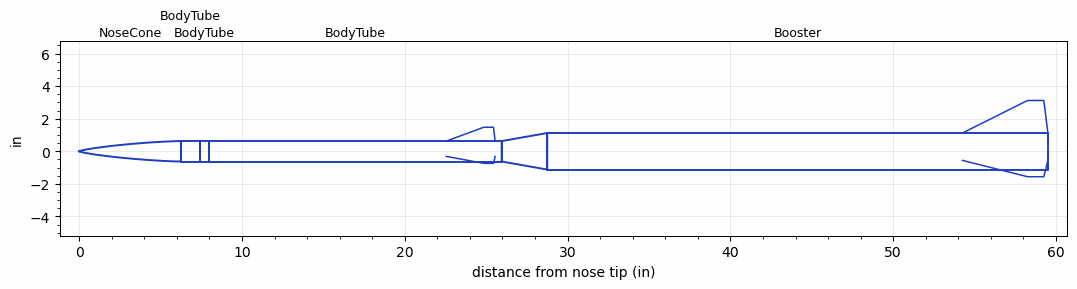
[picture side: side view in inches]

<RASAeroDocument>
 <FileVersion>2</FileVersion>
 <RocketDesign>
  <NoseCone>
   <Length>6.25</Length>
   <Diameter>1.255</Diameter>
   <Shape>Von Karman Ogive</Shape>
   <Location>0</Location>
  </NoseCone>
  <BodyTube>
   <Length>1.2</Length>
   <Diameter>1.255</Diameter>
   <Location>6.25</Location>
  </BodyTube>
  <BodyTube>
   <Length>0.5</Length>
   <Diameter>1.255</Diameter>
   <Location>7.45</Location>
  </BodyTube>
  <BodyTube>
   <Length>18</Length>
   <Diameter>1.255</Diameter>
   <Location>7.95</Location>
   <Fin>
    <Count>3</Count>
    <Chord>3</Chord>
    <Span>0.85</Span>
    <SweepDistance>2.3</SweepDistance>
    <TipChord>0.6</TipChord>
    <Thickness>0.096</Thickness>
    <LERadius>0.015</LERadius>
    <Location>3.4</Location>
    <AirfoilSection>Hexagonal</AirfoilSection>
    <FX1>0.15</FX1>
    <FX3>0.15</FX3>
   </Fin>
  </BodyTube>
  <Booster>
   <Length>30.75</Length>
   <Diameter>2.242</Diameter>
   <InsideDiameter>1.255</InsideDiameter>
   <RailGuideDiameter>0.438</RailGuideDiameter>
   <RailGuideHeight>0.298</RailGuideHeight>
   <Location>25.95</Location>
   <ShoulderLength>2.8</ShoulderLength>
   <Fin>
    <Count>3</Count>
    <Chord>5.25</Chord>
    <Span>2</Span>
    <SweepDistance>4</SweepDistance>
    <TipChord>1</TipChord>
    <Thickness>0.096</Thickness>
    <LERadius>0.015</LERadius>
    <Location>5.25</Location>
    <AirfoilSection>Hexagonal</AirfoilSection>
    <FX1>0.2</FX1>
    <FX3>0.2</FX3>
   </Fin>
  </Booster>
  <Surface>Camouflage Paint</Surface>
  <ModifiedBarrowman>True</ModifiedBarrowman>
  <Turbulence>True</Turbulence>
  <UseBooster1>True</UseBooster1>
  <UseBooster2>False</UseBooster2>
 </RocketDesign>
 <LaunchSite>
  <Altitude>850</Altitude>
  <Pressure>29.02</Pressure>
  <RodAngle>2</RodAngle>
  <RodLength>6</RodLength>
  <Temperature>55.97</Temperature>
  <WindSpeed>8</WindSpeed>
 </LaunchSite>
 <Recovery>
  <Altitude1>656.168</Altitude1>
  <Altitude2>700</Altitude2>
  <DeviceType1>Parachute</DeviceType1>
  <DeviceType2>Parachute</DeviceType2>
  <Event1>True</Event1>
  <Event2>True</Event2>
  <Size1>9</Size1>
  <Size2>24</Size2>
  <EventType1>Apogee</EventType1>
  <EventType2>Altitude</EventType2>
  <CD1>0.5</CD1>
  <CD2>0</CD2>
 </Recovery>
 <SimulationList>
  <Simulation>
   <SustainerEngine>Dart  (NoThrust)</SustainerEngine>
   <SustainerLaunchWt>1.32</SustainerLaunchWt>
   <SustainerCG>14.08</SustainerCG>
   <SustainerIgnitionDelay>0</SustainerIgnitionDelay>
   <Booster1Engine>J540R  (AT)</Booster1Engine>
   <Booster1LaunchWt>5.96</Booster1LaunchWt>
   <Booster1SeparationDelay>0</Booster1SeparationDelay>
   <Booster1IgnitionDelay>0</Booster1IgnitionDelay>
   <Booster1CG>38</Booster1CG>
   <IncludeBooster1>True</IncludeBooster1>
   <Booster2Delay>0</Booster2Delay>
   <IncludeBooster2>False</IncludeBooster2>
   <TimetoApogee>21.33034</TimetoApogee>
   <MaxAltitude>9448.087</MaxAltitude>
   <MaxVelocity>1171.424</MaxVelocity>
  </Simulation>
  <Simulation>
   <SustainerEngine>Dart  (NoThrust)</SustainerEngine>
   <SustainerLaunchWt>1.23</SustainerLaunchWt>
   <SustainerCG>13.2</SustainerCG>
   <SustainerIgnitionDelay>0</SustainerIgnitionDelay>
   <Booster1Engine>J449BS  (CTI)</Booster1Engine>
   <Booster1LaunchWt>5.95</Booster1LaunchWt>
   <Booster1SeparationDelay>0</Booster1SeparationDelay>
   <Booster1IgnitionDelay>0</Booster1IgnitionDelay>
   <Booster1CG>38.4</Booster1CG>
   <IncludeBooster1>True</IncludeBooster1>
   <Booster2Delay>0</Booster2Delay>
   <IncludeBooster2>False</IncludeBooster2>
   <TimetoApogee>23.11037</TimetoApogee>
   <MaxAltitude>10923.64</MaxAltitude>
   <MaxVelocity>1266.204</MaxVelocity>
  </Simulation>
  <Simulation>
   <SustainerEngine>Dart  (NoThrust)</SustainerEngine>
   <SustainerLaunchWt>1.28</SustainerLaunchWt>
   <SustainerCG>11.27</SustainerCG>
   <SustainerIgnitionDelay>0</SustainerIgnitionDelay>
   <Booster1Engine>J760-WT-19A  (CTI)</Booster1Engine>
   <Booster1LaunchWt>5.9</Booster1LaunchWt>
   <Booster1SeparationDelay>0</Booster1SeparationDelay>
   <Booster1IgnitionDelay>0</Booster1IgnitionDelay>
   <Booster1CG>38.8</Booster1CG>
   <IncludeBooster1>True</IncludeBooster1>
   <Booster2Delay>0</Booster2Delay>
   <IncludeBooster2>False</IncludeBooster2>
   <TimetoApogee>22.99039</TimetoApogee>
   <MaxAltitude>11204.15</MaxAltitude>
   <MaxVelocity>1428.314</MaxVelocity>
  </Simulation>
  <Simulation>
   <SustainerEngine>G75J  (AT)</SustainerEngine>
   <SustainerLaunchWt>1.8</SustainerLaunchWt>
   <SustainerCG>14.12</SustainerCG>
   <SustainerIgnitionDelay>0</SustainerIgnitionDelay>
   <Booster1Engine>J760-WT-19A  (CTI)</Booster1Engine>
   <Booster1LaunchWt>6.4</Booster1LaunchWt>
   <Booster1SeparationDelay>0</Booster1SeparationDelay>
   <Booster1IgnitionDelay>0</Booster1IgnitionDelay>
   <Booster1CG>37.38</Booster1CG>
   <IncludeBooster1>True</IncludeBooster1>
   <Booster2Delay>0</Booster2Delay>
   <IncludeBooster2>False</IncludeBooster2>
   <TimetoApogee>28.0205</TimetoApogee>
   <MaxAltitude>16573.13</MaxAltitude>
   <MaxVelocity>1517.604</MaxVelocity>
  </Simulation>
  <Simulation>
   <SustainerEngine>Dart  (NoThrust)</SustainerEngine>
   <SustainerLaunchWt>1.27</SustainerLaunchWt>
   <SustainerCG>11.18</SustainerCG>
   <SustainerIgnitionDelay>0</SustainerIgnitionDelay>
   <Booster1Engine>K530SS  (CTI)</Booster1Engine>
   <Booster1LaunchWt>7.12</Booster1LaunchWt>
   <Booster1SeparationDelay>0</Booster1SeparationDelay>
   <Booster1IgnitionDelay>0</Booster1IgnitionDelay>
   <Booster1CG>40.54</Booster1CG>
   <IncludeBooster1>True</IncludeBooster1>
   <Booster2Delay>0</Booster2Delay>
   <IncludeBooster2>False</IncludeBooster2>
   <TimetoApogee>23.54038</TimetoApogee>
   <MaxAltitude>11219.02</MaxAltitude>
   <MaxVelocity>1350.228</MaxVelocity>
  </Simulation>
  <Simulation>
   <SustainerEngine>Dart  (NoThrust)</SustainerEngine>
   <SustainerLaunchWt>1.27</SustainerLaunchWt>
   <SustainerCG>11.19</SustainerCG>
   <SustainerIgnitionDelay>0</SustainerIgnitionDelay>
   <Booster1Engine>J800T  (AT)</Booster1Engine>
   <Booster1LaunchWt>5.9</Booster1LaunchWt>
   <Booster1SeparationDelay>0</Booster1SeparationDelay>
   <Booster1IgnitionDelay>0</Booster1IgnitionDelay>
   <Booster1CG>38.95</Booster1CG>
   <IncludeBooster1>True</IncludeBooster1>
   <Booster2Delay>0</Booster2Delay>
   <IncludeBooster2>False</IncludeBooster2>
   <TimetoApogee>22.87038</TimetoApogee>
   <MaxAltitude>11043.82</MaxAltitude>
   <MaxVelocity>1324.655</MaxVelocity>
  </Simulation>
 </SimulationList>
</RASAeroDocument>
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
